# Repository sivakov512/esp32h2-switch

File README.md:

# Matter-Enabled Thread Switch on ESP32-H2

This repository contains a minimal Matter + Thread project targeting the **ESP32-H2** MCU. It controls a relay with the aim of managing a water heater or similar appliance. The project is written in **C++20** (with some C code) using the **ESP-IDF** and **ESP-Matter** frameworks.

## Overview
* **Core MCU**: [ESP32-H2](https://www.espressif.com/en/products/socs/esp32-h2)
* **Protocol**: Matter over Thread
* **Relay Control**: GPIO27
* **Status LED**: GPIO26
* **Language**: C++20 & C
* **Thread Config**: Enabled by default in sdkconfig.defaults
* **Commissioning Data**: Stored in a factory partition (fctry) at 0x3E0000

## Hardware

### Board Overview

The ESP32-H2 Switch is designed for controlling high-voltage appliances with safety in mind. The board features:

- Compact dimensions for easy installation
- Clearly labeled connectors and indicators
- High-quality relay rated for 220V and up to 10A current

### Dimensions & Mounting

The board measures 54.56mm x 28.64mm and is designed to be installed inside existing devices or enclosures.

### Pinout & Connections

Important connections:
- **AC Input/Output**: Screw terminals on the left side for line (phase) and neutral input and output
- **Status LEDs**: Located at the bottom above the antenna
  - LED_RELAY: Indicates relay activation status
  - LED_RUN: Indicates device operational status
- **Debug Headers**: UART pins for flashing and debugging (from top to bottom: +3.3V, TX, RX, GND)
- **Control Pins**: BOOT and RESET pins (must be manually shorted to GND to activate)

**Safety Note**: All power lines are routed on the bottom layer of the PCB. Exercise extreme caution during installation to avoid contact with these traces when connected to mains power.

### Hardware Variants
The project includes KiCad PCB and schematic files in the `hardware/` directory with two variants:
- `smd/`: Surface-mounted component design (more compact)
- `tht/`: Through-hole component design (easier to assemble manually)

**Note**: The hardware designs depend on a custom KiCad component library. To open and edit the schematics:
1. Install the component library from https://github.com/sivakov512/kicad-library
2. Follow the installation instructions in that repository

## Software

### Requirements
1. [ESP-IDF 5.4](https://github.com/espressif/esp-idf/tree/release/v5.4)
    - Follow the official ESP-IDF [documentation](https://docs.espressif.com/projects/esp-idf/en/stable/esp32h2/get-started/index.html#installation) for installation and setup.
2. [ESP-Matter 1.4](https://github.com/espressif/esp-matter/tree/release/v1.4)
    - Refer to the ESP-Matter repo for detailed instructions on integrating Matter into ESP-IDF.

### Setup

1. Clone this repository alongside your ESP-IDF and ESP-Matter installations.
2. Ensure that `sdkconfig.defaults` includes the necessary Thread and Matter configurations for ESP32-H2.
3. Verify that `GPIO27` is free to drive your relay hardware and `GPIO26` for the status LED.

### Project Structure
Typical ESP-IDF directory layout:
```project_root/
├── CMakeLists.txt
├── sdkconfig.defaults
├── main/
│   ├── main.cpp
│   └── ...
├── hardware/
│   ├── smd/
│   └── tht/
├── docs/
│   └── images/
└── partitions.csv
```

### Building

1. Set the target to **esp32h2**:
```sh
idf.py set-target esp32h2
```

2. Build the firmware:
```sh
idf.py build
```

3. Flash to your device (initial firmware, excluding commissioning info):
```sh
idf.py flash
```

### Commissioning Data (Factory Partition)

To avoid using test keys in production, generate your own commissioning data and flash it to the `fctry` partition at address `0x3E0000`.
* We recommend using [ESP Matter Manufacturing Tool (mfg_tool)](https://github.com/espressif/esp-matter-tools/tree/main/mfg_tool).
* Example command (using test keys) for building provisioning data:
```sh
esp-matter-mfg-tool -v 0xFFF2 -p 0x8001 \
  --vendor-name "Nikita Sivakov" \
  --product-name "Switch" \
  -cd $MATTER_SDK_PATH/credentials/test/certification-declaration/Chip-Test-CD-FFF2-8001.der
```
This generates a binary that contains the necessary credentials for Matter commissioning.

#### Flashing the Commissioning Binary
Once the binary is generated, flash it to `0x3E0000`:
```sh
esptool.py -p <DEVICE_PORT> write_flash 0x3E0000 <PATH_TO_GENERATED_BINARY>
```
*Replace `<DEVICE_PORT>` (e.g. `COM3` or `/dev/ttyUSB0`) and `<PATH_TO_GENERATED_BINARY>` with your actual values.*

## Usage and Operation

### Initial Setup
1. Mount the board in a suitable enclosure.
2. Connect the power and load wires according to the pinout diagram.
3. Power up the board.

### Software Setup
1. Join a Thread network and start the Matter commissioning process.
2. Use a Matter controller (Apple Home, Google Home, or other Matter-compatible hub) to add the device.
3. Once commissioned, toggle the relay through Matter commands.

### Status Indicators
- **LED_RUN**: Indicates that the device is operating properly
- **LED_RELAY**: Indicates when the relay is activated

## Contributing
* For any issues, suggestions, or feature requests, please open an [issue](../../issues).
* Pull requests with improvements or bug fixes are welcome.

## Safety Warning

**IMPORTANT**: This device controls high-voltage appliances. Improper installation may result in electric shock or fire hazards.

- Always disconnect power before installation or maintenance
- Install in a suitable enclosure
- Follow all local electrical codes and regulations
- If you're not qualified to work with high-voltage equipment, consult a licensed electrician

---

**Note**: This project is provided as-is for demonstration purposes. Always exercise caution when dealing with high-voltage equipment such as water heaters.

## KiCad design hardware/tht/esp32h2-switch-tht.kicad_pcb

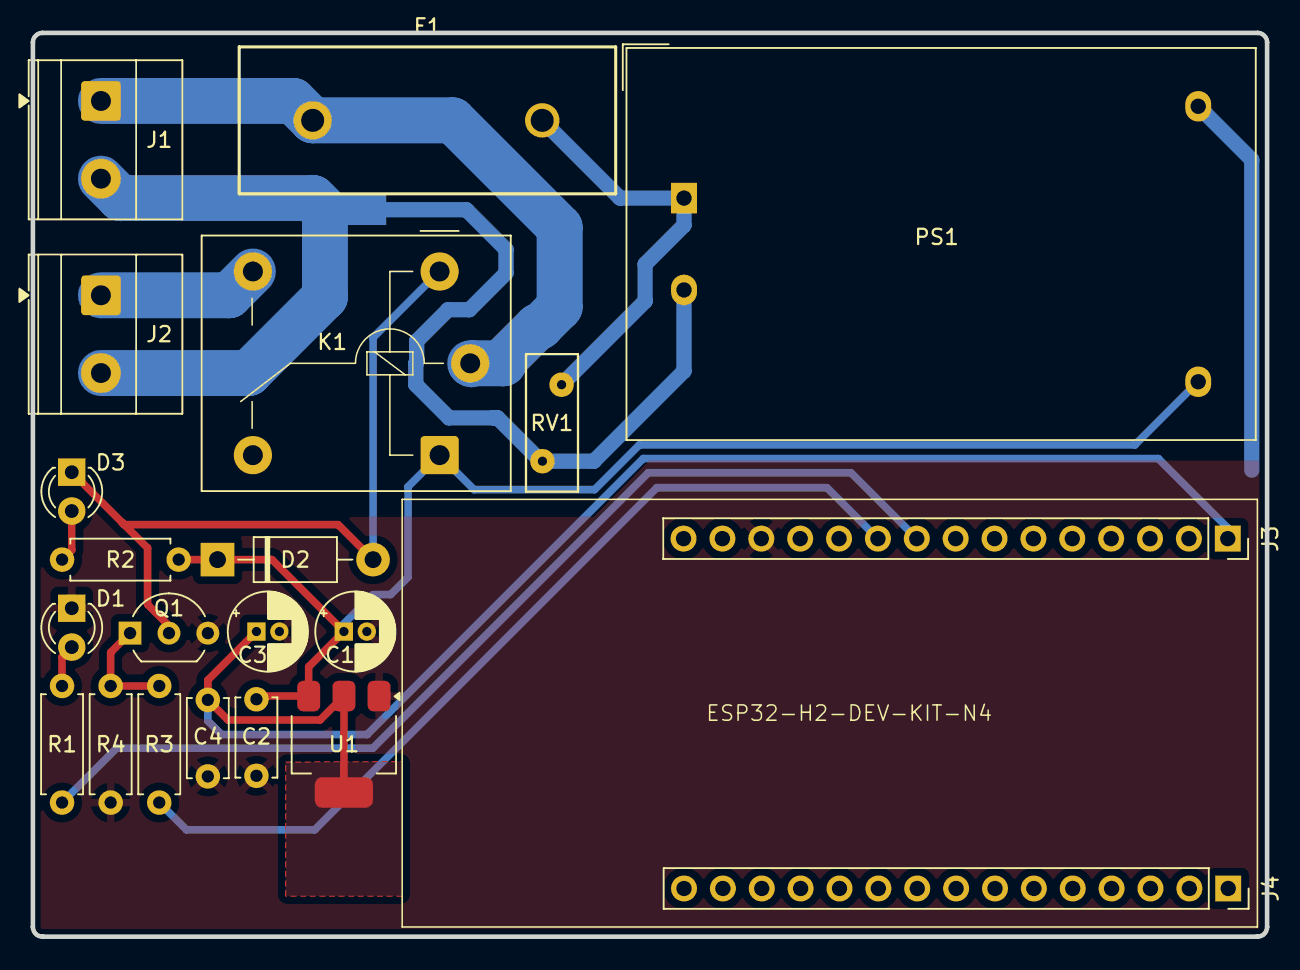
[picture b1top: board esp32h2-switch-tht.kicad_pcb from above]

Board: 2 copper layers, 80.6 x 59.1 mm, 22 parts (1 on the bottom side), 14 nets.

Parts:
C1, C3: 22u; CP_Radial_D5.0mm_P1.50mm
C2, C4: 100n; C_Disc_D5.0mm_W2.5mm_P5.00mm
D1: Blue, 3V, 10mA; LED_D3.0mm
D2: 40V, 1A; D_DO-41_SOD81_P10.16mm_Horizontal
D3: Red, 2V, 10mA; LED_D3.0mm
F1: T250mA 250V; FuseHolder_THT_5x20mm_PTF76_RM15mm
J1, J2: Screw_Terminal_01x02; TerminalBlock_Phoenix_MKDS-1,5-2-5.08_1x02_P5.08mm_Horizont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
J3, J4: Conn_01x15; PinSocket_1x15_P2.54mm_Vertical
K1: SPDT, 5V 72R, 10A 250VAC; Relay_SPDT_Relpol-RM51
NT1: NetTie_2; NetTie-2_SMD_Pad2.0mm
PS1: HLK-5M05; Converter_ACDC_Hi-Link_HLK-5Mxx
Q1: NPN, 40V, 500mA; TO-92_Inline_Wide
R1: 220R; R_Axial_DIN0207_L6.3mm_D2.5mm_P7.62mm_Horizontal
R2, R3: 330R; R_Axial_DIN0207_L6.3mm_D2.5mm_P7.62mm_Horizontal
R4: 10k; R_Axial_DIN0207_L6.3mm_D2.5mm_P7.62mm_Horizontal
RV1: 275V; RV_Disc_D9mm_W3.4mm_P5mm
U1: LM1117MP-3.3; SOT-223-3_TabPin2

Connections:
+3.3V: C3.1, C4.1, J3.1, U1.2 (VO)
+5V: C1.1, C2.1, D2.1 (K), K1.A2, PS1.4 (+Vout), R2.1, U1.3 (VI)
/LED_RELAY: D3.2 (A), R2.2
/LED_RUN: D1.2 (A), R1.1
/L_OUT: J2.1, K1.14
/RELAY_COIL: D2.2 (A), D3.1 (K), K1.A1, Q1.2 (C)
/RELAY_CTRL: J3.10, R3.1
GND: C1.2, C2.2, C3.2, C4.2, D1.1 (K), J3.13, PS1.3 (-Vout), Q1.3 (E), R4.2, U1.1 (GND)
L: F1.2, PS1.1 (AC/L), RV1.1
L_IN: F1.1, J1.1, K1.11
N: NT1.2, PS1.2 (AC/N), RV1.2
N_IN: J1.2, J2.2, NT1.1
unnamed: J3.9, R1.2
unnamed: Q1.1 (B), R3.2, R4.1

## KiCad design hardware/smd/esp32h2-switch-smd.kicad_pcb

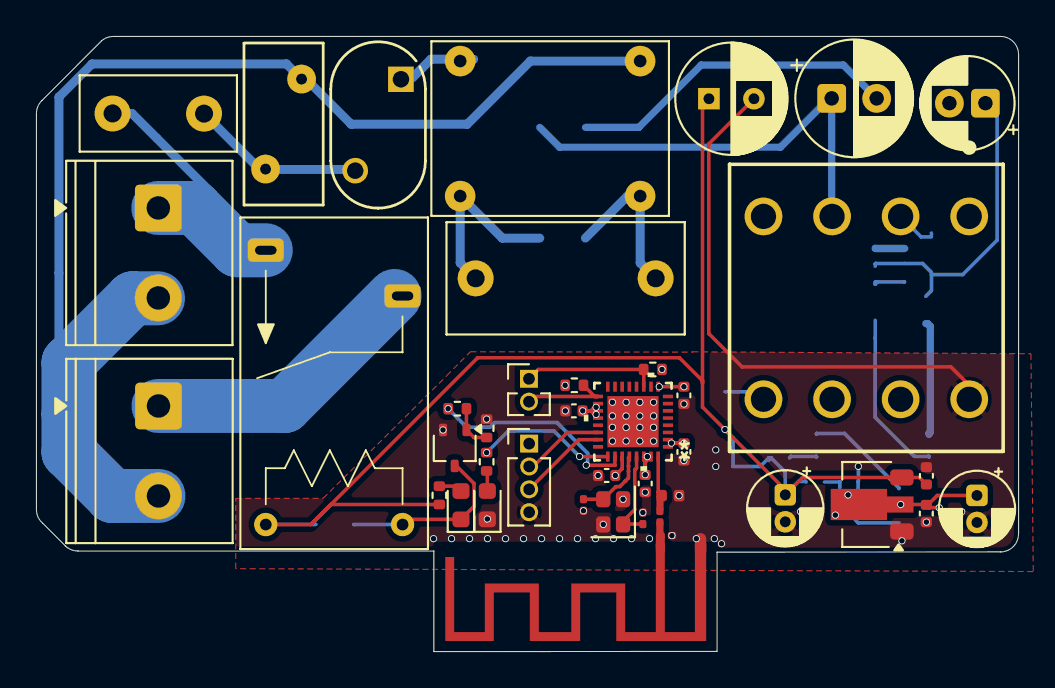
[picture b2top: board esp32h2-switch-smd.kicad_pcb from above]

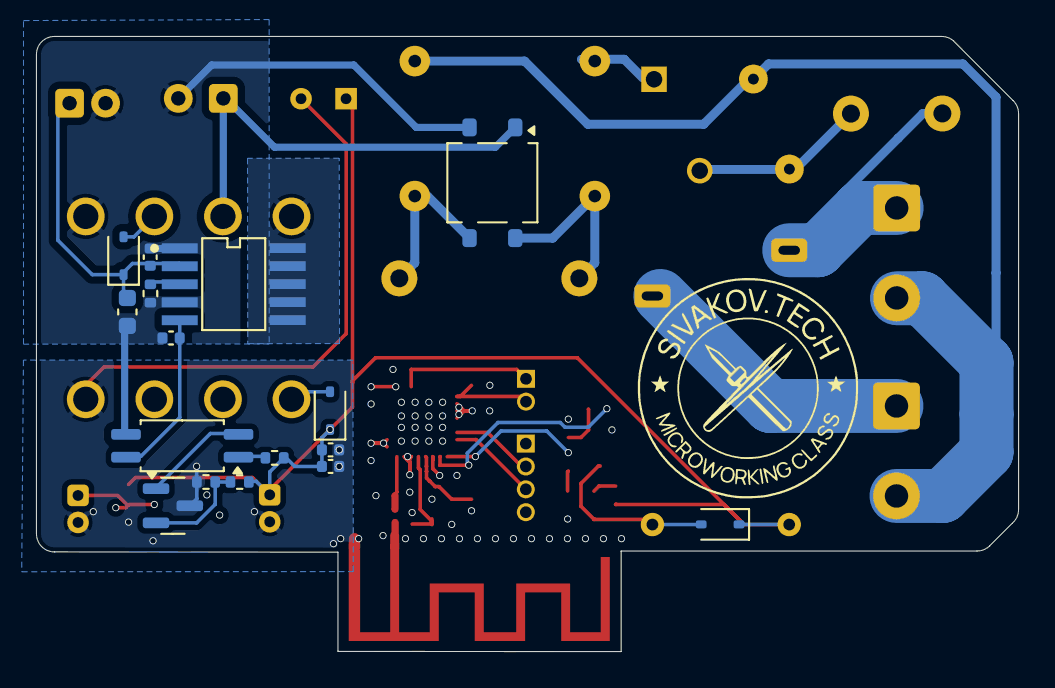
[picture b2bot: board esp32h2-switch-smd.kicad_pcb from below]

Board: 4 copper layers, 54.6 x 34.2 mm, 59 parts (18 on the bottom side), 33 nets.

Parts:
AE1: Antenna_Chip; Antenna_PCB_Espressif_2.4GHz_Right
C1, C5: 22u 10V; CP_Radial_D4.0mm_P1.50mm
C2, C6, C10, C14, C16, C19, C20, C22: 100n 10V X7R; C_0402_1005Metric
C3: 220n 275V X2; C_Rect_L13.0mm_W6.0mm_P10.00mm_FKS3_FKP3_MKS4
C4: 4.7u 400V; CP_Radial_D6.3mm_P2.50mm
C7: 2.2n 50V X7R; C_0402_1005Metric
C8: 470u 10V; CP_Radial_D6.0mm_P2.50mm
C9: 22u 35V; CP_Radial_D5.0mm_P2.00mm
C11: 100n 35V X7R; C_0603_1608Metric
C12: 1n 10V X7R; C_0402_1005Metric
C13: 2.2n 35V X7R; C_0402_1005Metric
C15: 5.6p C0G; C_0201_0603Metric
C17, C21: 8p 10V C0G; C_0201_0603Metric
C18: 2.2p C0G; C_0201_0603Metric
D1: 1A 600V; TO-269AA
D2, D3, D4: 40V 1A; D_SOD-323
D5: Blue, 3V, 10mA; LED_0603_1608Metric
D6: Red, 2V, 10mA; LED_0603_1608Metric
F1: T500mA 250V; Fuse_Littelfuse_395Series
FL1: 2×4.7m ≥0.3A ≤2R; TDK_B82720K_Vertical_13x9.5mm_P10x7.5mm
J1, J2: Screw_Terminal_01x02; TerminalBlock_Phoenix_PT-1,5-2-5.0-H_1x02_P5.00mm_Horizontal
J5: UART; PinHeader_1x04_P1.27mm_Vertical
J6: Conn_01x02_Pin; PinHeader_1x02_P1.27mm_Vertical
K1: SPST, 5V 72R, 10A 250VAC; OJ_SH_105HM_SPST
L1: 3.9 nH; L_0402_1005Metric
NT1, NT2: NetTie_2; NetTie_2_D0.5_P4.0
Q1: NPN, 40V, 500mA; SOT-323_SC-70
R1: 30k; R_0402_1005Metric
R2: 470R; R_0402_1005Metric
R3, R4, R7, R9, R10: 10k; R_0402_1005Metric
R5, R8: 330R; R_0402_1005Metric
R6: 220R; R_0402_1005Metric
RV1: 275V; RV_Disc_D9mm_W4.4mm_P5mm
T1: Wurth 750370423; Wurth_750370423_THT_E13
TH1: 10R 25C; NTC10D_7_Disc_D7.0mm_P5.0mm
U1: LM1117F-3.3; SOT-89-3
U2: VIPER06; STMicroelectronics_VIPER06_SSO10
U3: EL3H7; SSOP-4_4.4x2.6mm_P1.27mm
U4: TL431; SOT-23
U5: ESP32-H2; TQFN_32_1EP_4x4mm_P0.4mm_EP2.4x2.4mm_Compact
Y1: 32MHz ±10ppm CL8pF; Crystal_SMD_2016-4Pin_2.0x1.6mm

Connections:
+3.3V: C5.1, C6.1, C14.2, C16.2, C19.2, C20.2, C22.2, J5.1, R7.2, R10.2, U1.2 (VO), U5.1 (VDD3P3), U5.2 (VDD3P3), U5.9 (VDDPST1), U5.18 (VBAT), U5.19 (VDDA_PMU), U5.20 (VDDPST1), U5.27 (VDD3P3), U5.30 (VDD3P3), U5.31 (VDD3P3)
+5V: C1.1, C2.1, C8.1, C10.1, C12.1, D3.1 (K), D4.1 (K), K1.A1, R2.2, R3.1, R5.1, U1.3 (VI)
/Control unit/LED_RELAY: D6.2 (A), R5.2
/Control unit/LED_RUN: R6.2, U5.25 (GPIO26)
/Control unit/RELAY_COIL: D4.2 (A), D6.1 (K), K1.A2, Q1.3 (C)
/Control unit/RELAY_CTRL: R8.1, U5.26 (GPIO27)
/Control unit/RF: C15.2, L1.1, U5.32 (ANT)
/Control unit/RX: J5.3, U5.23 (U0TXD)
/Control unit/TX: J5.2, U5.22 (U0RXD)
/N_IN: J1.2, J2.2, NT2.1
/Power supply/DRAIN: T1.4, U2.6 (DRAIN), U2.7 (DRAIN), U2.8 (DRAIN), U2.9 (DRAIN), U2.10 (DRAIN)
/Power supply/VRECT: C4.1, D1.1 (+), T1.3
BOOT: J6.1, R7.1, U5.11 (GPIO9)
GND: AE1.2 (PCB_Trace), C1.2, C2.2, C5.2, C6.2, C8.2, C10.2, C12.2, C14.1, C16.1, C17.2, C18.1, C19.1, C20.1, C21.1, C22.1, D5.1 (K), J5.4, L1.2, Q1.2 (E), R4.2, R9.2, T1.8, U1.1 (GND), U4.3 (A), U5.33 (GND), Y1.2, Y1.4
GND_P: C4.2, C7.2, C9.2, C11.2, C13.2, D1.2 (-), R1.2, T1.1, U2.1 (GND), U2.4 (FB), U3.3
L: C3.1, D1.4, F1.1, F1.2, FL1.1, FL1.4, NT1.2, RV1.1, TH1.1, TH1.2
L_IN: J1.1, K1.14, NT1.1
L_OUT: J2.1, K1.13
N: C3.2, D1.3, FL1.2, FL1.3, NT2.2, RV1.2
unnamed: AE1.1 (FEED), C15.1, C18.2
unnamed: D2.2 (A), T1.2
unnamed: C9.1, C11.1, C13.1, D2.1 (K), U2.2 (VDD)
unnamed: D3.2 (A), T1.5
unnamed: D5.2 (A), R6.1
unnamed: Q1.1 (B), R8.2, R9.1
unnamed: R2.1, U3.1
unnamed: C7.1, U2.5 (COMP), U3.4
unnamed: R1.1, U2.3 (LIM)
unnamed: U3.2, U4.1 (K)
unnamed: R3.2, R4.1, U4.2 (REF)
unnamed: C21.2, U5.28 (XTAL_N), Y1.3
unnamed: C17.1, U5.29 (XTAL_P), Y1.1
RESET: J6.2, R10.1, U5.17 (CHIP_EN)

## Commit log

2025-02-12 New project boilerplate
2025-02-16 Some docs
2025-02-16 Implement thread switch
2025-03-27 Ignore some stuff
2025-03-27 Add compile_commands.json symlink
2025-03-27 KiCad schemas
2025-04-01 Replace devkit on schema with header pings
2025-04-01 Use schemas specific gitignore
2025-04-01 ERC checks
2025-04-02 Add footprints to schematic
2025-04-02 Do not track kicad projects settings
2025-04-02 Define AC net class
2025-04-02 Ignore autosave files (so tired of huge amount of files that don't need to be tracked)
2025-04-04 PCB schematic
2025-04-04 Fix nets due to checks
2025-04-05 Better arragement components + more copper fields
2025-04-10 Add LED control to driver
2025-04-15 Better layout for hand soldering
2025-04-21 Add two calibration vias to the PCB layout
2025-04-27 Fix footprints and improve layout for hand soldering
2025-04-27 Replace HLK block with SMPS
2025-05-01 Improve layout a lot
2025-05-01 Reorganize KiCad project into hardware directory
2025-05-01 Update .gitignore to include additional IDE and build files
2025-05-01 Update some project definitions and exclude backups from tracking
2025-05-06 Separate schematics into two sheets. And make them done, yep
2025-05-06 Add capacitor specifications, change capacity around crystal
2025-05-06 Properly layout GND-fed antenna
2025-05-06 Drop all tht legacy footprints
2025-05-08 Assign footprints and JLC numbers (plus minor changes)
2025-05-08 Bill of materials
2025-05-20 Complete PCB and schematics after fucking a lot of iterations
2025-05-22 Rename JLCPCB property to LCSC PN across schematic files
2025-05-22 Add fabrication toolkit config
2025-05-22 Update library paths from KiCadX to PCM_SKC
2025-05-22 Relink symbols and footprints to new lib and fix few errors
2025-05-24 Added logo on silkscreen
2025-05-24 Use all active layers in fabrication toolkit
2025-05-24 Make vias a bit bigger because of JLCPCB prices and change out-of-stock component
2025-06-04 Update GPIO pin assignments for relay and LED
2025-06-04 Add a user layer with pinout
2025-06-04 Hardware documentation
2025-06-05 Fix typo in capacitors for oscillator
